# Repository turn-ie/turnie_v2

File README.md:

# turnie v2

ESP32-C3-MINI-1 と 64 個の WS2812B-2020（8x8）を 1 枚の基板に載せた turnie。

## ディレクトリ構成

| ディレクトリ | 内容 |
|---|---|
| `hardware/` | KiCad プロジェクト（`turnie_v2.kicad_pro`）、部品配置（`turnie_v2-all-pos.csv`） |
| `hardware/jlcpcb/` | JLCPCB に入稿したガーバーと PCBA 用ファイル |
| `hardware/*.pretty` | 自作フットプリント（EVQ-VVD00203B、サムホイール型可変抵抗） |

## ハードウェア

| 部品 | 内容 |
|---|---|
| MCU | ESP32-C3-MINI-1 |
| LED | WS2812B-2020 x 64（8x8） |
| 電源 | MIC5219-3.3（LDO）、USB-C |
| 入力 | タクトスイッチ x 3、サムホイール |

## 備考

- この版向けのファームウェアは収録していない。
- 画像は KiCad の 3D ビューから書き出したもの。

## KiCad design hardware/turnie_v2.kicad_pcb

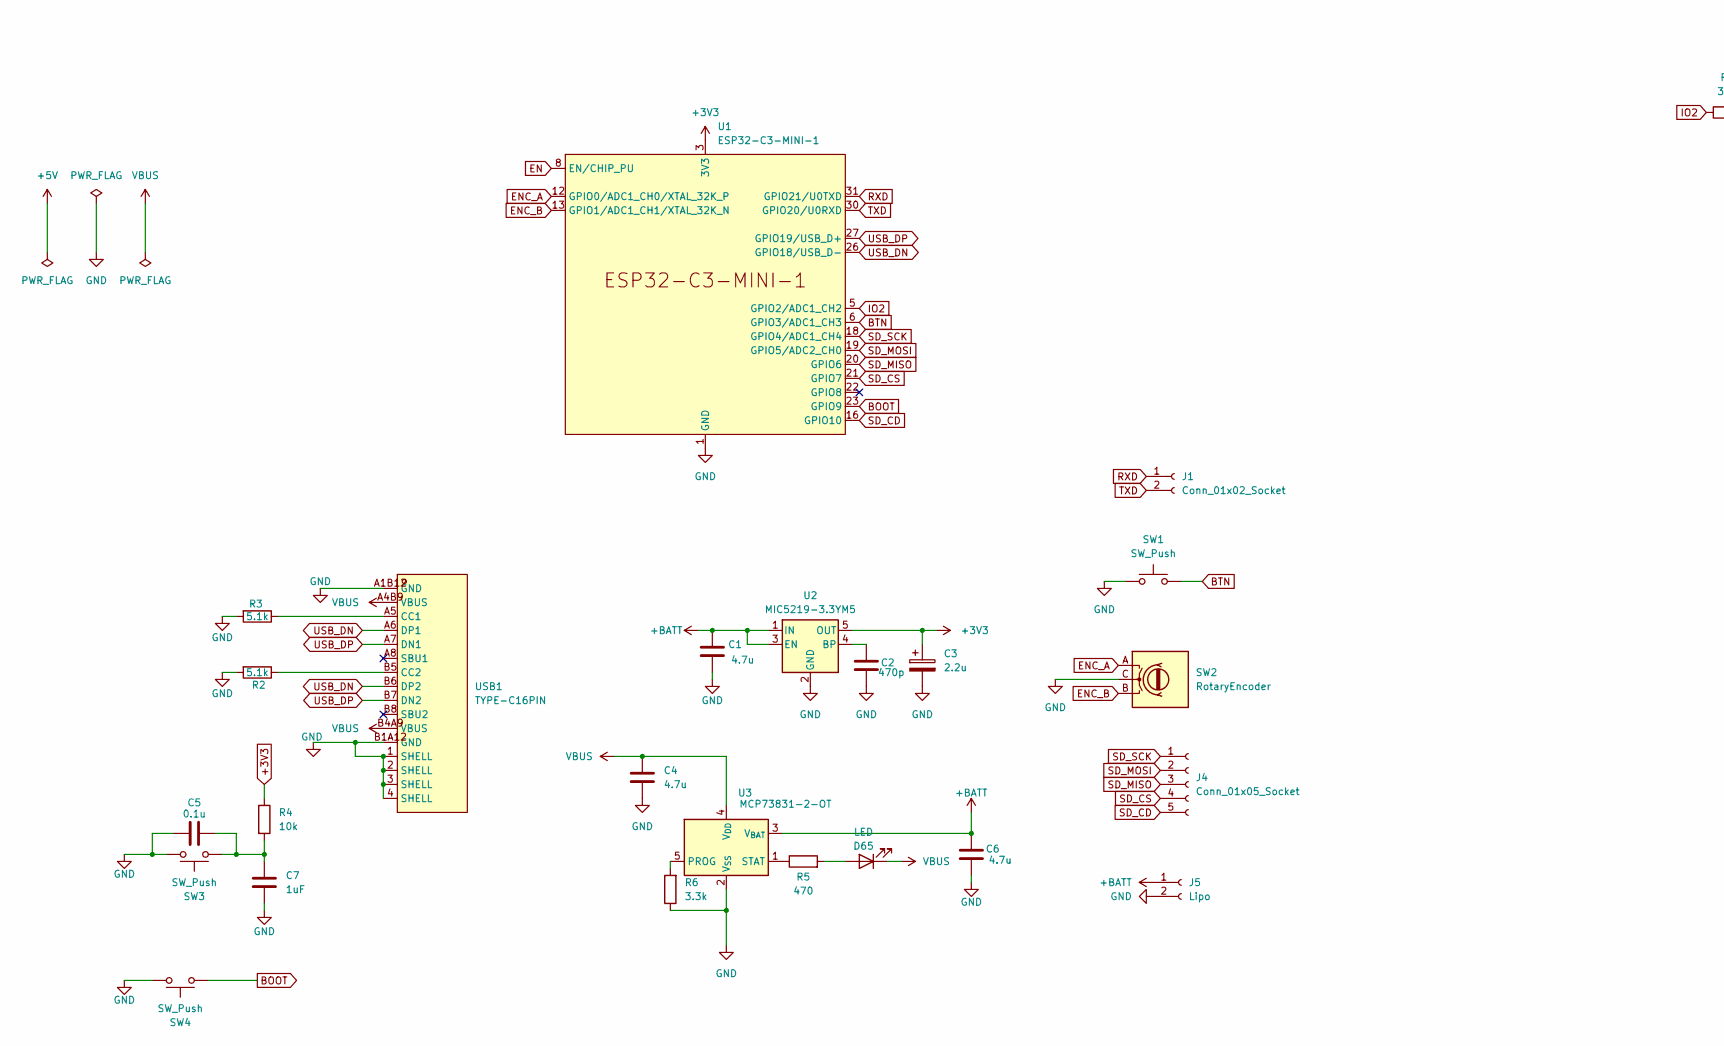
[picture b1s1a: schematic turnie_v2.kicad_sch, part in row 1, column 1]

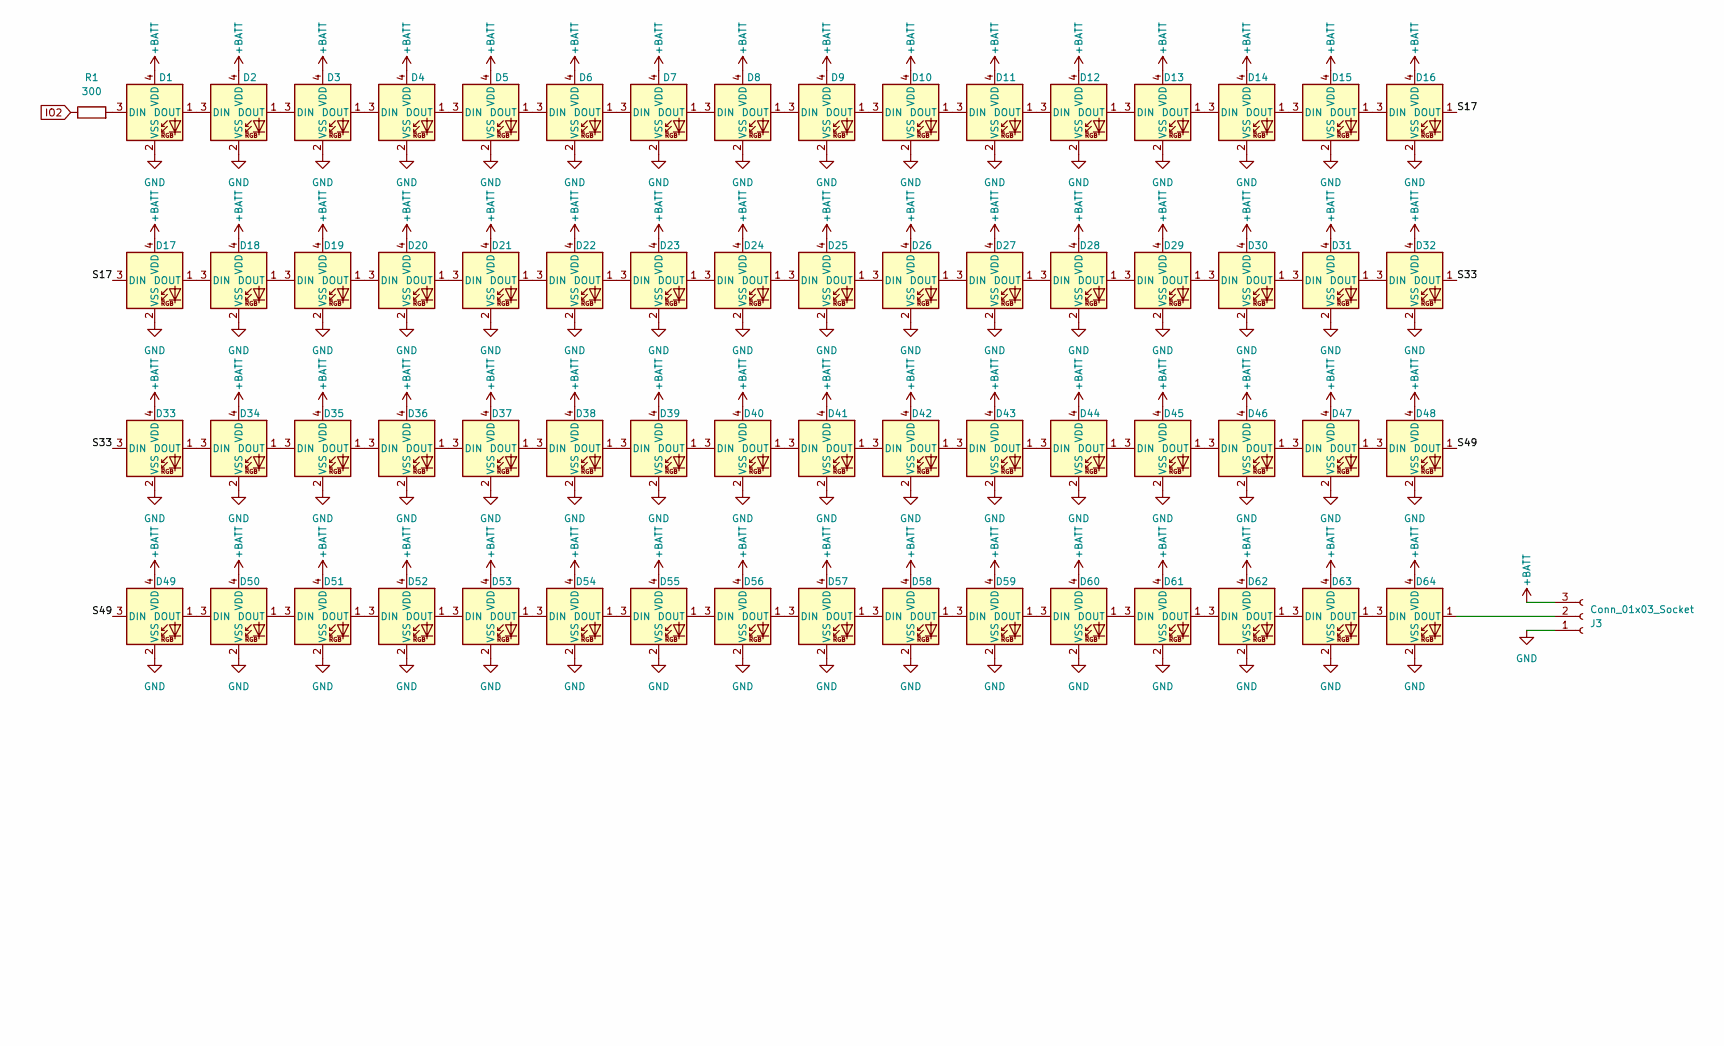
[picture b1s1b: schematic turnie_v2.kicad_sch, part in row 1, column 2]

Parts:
C1, C4, C6: 4.7u; C_0805_2012Metric
C2: 470p; C_0805_2012Metric
C3: 2.2u; C_0805_2012Metric
C5: 0.1u; C_0805_2012Metric
C7: 1uF; C_0402_1005Metric
D1, D2, D3, D4, D5, D6, D7, D8, D9, D10, D11, D12, D13, D14, D15, D16, D17, D18, D19, D20, D21, D22, D23, D24, D25, D26, D27, D28, D29, D30, D31, D32, D33, D34, D35, D36, D37, D38, D39, D40, D41, D42, D43, D44, D45, D46, D47, D48, D49, D50, D51, D52, D53, D54, D55, D56, D57, D58, D59, D60, D61, D62, D63, D64: WS2812B-2020; LED_WS2812B-2020_PLCC4_2.0x2.0mm
D65: LED; C_0805_2012Metric
J1: Conn_01x02_Socket; PinHeader_1x02_P2.54mm_Vertical
J3: Conn_01x03_Socket; PinSocket_1x03_P2.54mm_Vertical
J4: Conn_01x05_Socket; PinSocket_1x05_P2.54mm_Vertical
J5: Lipo; PinSocket_1x02_P2.54mm_Vertical
R1: 300; C_0402_1005Metric
R2, R3: 5.1k; C_0402_1005Metric
R4: 10k; C_0402_1005Metric
R5: 470; C_0402_1005Metric
R6: 3.3k; C_0402_1005Metric
SW1: SW_Push; SW_PUSH_6mm
SW2: RotaryEncoder; 名称未設定
SW3, SW4: SW_Push; SW_SPST_B3U-1000P
U1: ESP32-C3-MINI-1
U2: MIC5219-3.3YM5; SOT-23-5
U3: MCP73831-2-OT; SOT-23-5
USB1: TYPE-C16PIN; USB-C_SHOUHAN_TYPE-C16PIN_C393939; MPN TYPE-C16PIN; LCSC Part C393939

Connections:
+3V3: C3.1, R4.1, U1.3 (3V3), U2.5 (OUT)
+BATT: C1.1, C6.2, D1.4 (VDD), D2.4 (VDD), D3.4 (VDD), D4.4 (VDD), D5.4 (VDD), D6.4 (VDD), D7.4 (VDD), D8.4 (VDD), D9.4 (VDD), D10.4 (VDD), D11.4 (VDD), D12.4 (VDD), D13.4 (VDD), D14.4 (VDD), D15.4 (VDD), D16.4 (VDD), D17.4 (VDD), D18.4 (VDD), D19.4 (VDD), D20.4 (VDD), D21.4 (VDD), D22.4 (VDD), D23.4 (VDD), D24.4 (VDD), D25.4 (VDD), D26.4 (VDD), D27.4 (VDD), D28.4 (VDD), D29.4 (VDD), D30.4 (VDD), D31.4 (VDD), D32.4 (VDD), D33.4 (VDD), D34.4 (VDD), D35.4 (VDD), D36.4 (VDD), D37.4 (VDD), D38.4 (VDD), D39.4 (VDD), D40.4 (VDD), D41.4 (VDD), D42.4 (VDD), D43.4 (VDD), D44.4 (VDD), D45.4 (VDD), D46.4 (VDD), D47.4 (VDD), D48.4 (VDD), D49.4 (VDD), D50.4 (VDD), D51.4 (VDD), D52.4 (VDD), D53.4 (VDD), D54.4 (VDD), D55.4 (VDD), D56.4 (VDD), D57.4 (VDD), D58.4 (VDD), D59.4 (VDD), D60.4 (VDD), D61.4 (VDD), D62.4 (VDD), D63.4 (VDD), D64.4 (VDD), J3.3, J5.1, U2.1 (IN), U2.3 (EN), U3.3 (V_{BAT})
/S17: D16.1 (DOUT), D17.3 (DIN)
/S33: D32.1 (DOUT), D33.3 (DIN)
/S49: D48.1 (DOUT), D49.3 (DIN)
BOOT: SW4.2, U1.23 (GPIO9)
BTN: SW1.2, U1.6 (GPIO3/ADC1_CH3)
EN: U1.8 (EN/CHIP_PU)
ENC_A: SW2.A, U1.12 (GPIO0/ADC1_CH0/XTAL_32K_P)
ENC_B: SW2.B, U1.13 (GPIO1/ADC1_CH1/XTAL_32K_N)
GND: C1.2, C2.2, C3.2, C4.2, C5.1, C6.1, C7.2, D1.2 (VSS), D2.2 (VSS), D3.2 (VSS), D4.2 (VSS), D5.2 (VSS), D6.2 (VSS), D7.2 (VSS), D8.2 (VSS), D9.2 (VSS), D10.2 (VSS), D11.2 (VSS), D12.2 (VSS), D13.2 (VSS), D14.2 (VSS), D15.2 (VSS), D16.2 (VSS), D17.2 (VSS), D18.2 (VSS), D19.2 (VSS), D20.2 (VSS), D21.2 (VSS), D22.2 (VSS), D23.2 (VSS), D24.2 (VSS), D25.2 (VSS), D26.2 (VSS), D27.2 (VSS), D28.2 (VSS), D29.2 (VSS), D30.2 (VSS), D31.2 (VSS), D32.2 (VSS), D33.2 (VSS), D34.2 (VSS), D35.2 (VSS), D36.2 (VSS), D37.2 (VSS), D38.2 (VSS), D39.2 (VSS), D40.2 (VSS), D41.2 (VSS), D42.2 (VSS), D43.2 (VSS), D44.2 (VSS), D45.2 (VSS), D46.2 (VSS), D47.2 (VSS), D48.2 (VSS), D49.2 (VSS), D50.2 (VSS), D51.2 (VSS), D52.2 (VSS), D53.2 (VSS), D54.2 (VSS), D55.2 (VSS), D56.2 (VSS), D57.2 (VSS), D58.2 (VSS), D59.2 (VSS), D60.2 (VSS), D61.2 (VSS), D62.2 (VSS), D63.2 (VSS), D64.2 (VSS), J3.1, J5.2, R2.2, R3.2, R6.1, SW1.1, SW2.C, SW3.1, SW4.1, U1.1 (GND), U1.2 (GND), U1.11 (GND), U1.14 (GND), U1.36 (GND), U1.37 (GND), U1.38 (GND), U1.39 (GND), U1.40 (GND), U1.41 (GND), U1.42 (GND), U1.43 (GND), U1.44 (GND), U1.45 (GND), U1.46 (GND), U1.47 (GND), U1.48 (GND), U1.49 (GND), U1.50 (GND), U1.51 (GND), U1.52 (GND), U1.53 (GND), U2.2 (GND), U3.2 (V_{SS}), USB1.1 (SHELL), USB1.2 (SHELL), USB1.3 (SHELL), USB1.4 (SHELL), USB1.A1B12 (GND), USB1.B1A12 (GND)
IO2: R1.1, U1.5 (GPIO2/ADC1_CH2)
unnamed: C5.2, C7.1, R4.2, SW3.2
unnamed: D1.3 (DIN), R1.2
unnamed: D1.1 (DOUT), D2.3 (DIN)
unnamed: D2.1 (DOUT), D3.3 (DIN)
unnamed: D3.1 (DOUT), D4.3 (DIN)
unnamed: D4.1 (DOUT), D5.3 (DIN)
unnamed: D5.1 (DOUT), D6.3 (DIN)
unnamed: D6.1 (DOUT), D7.3 (DIN)
unnamed: D7.1 (DOUT), D8.3 (DIN)
unnamed: D8.1 (DOUT), D9.3 (DIN)
unnamed: D9.1 (DOUT), D10.3 (DIN)
unnamed: D10.1 (DOUT), D11.3 (DIN)
unnamed: D11.1 (DOUT), D12.3 (DIN)
unnamed: D12.1 (DOUT), D13.3 (DIN)
unnamed: D13.1 (DOUT), D14.3 (DIN)
unnamed: D14.1 (DOUT), D15.3 (DIN)
unnamed: D15.1 (DOUT), D16.3 (DIN)
unnamed: D17.1 (DOUT), D18.3 (DIN)
unnamed: D18.1 (DOUT), D19.3 (DIN)
unnamed: D19.1 (DOUT), D20.3 (DIN)
unnamed: D20.1 (DOUT), D21.3 (DIN)
unnamed: D21.1 (DOUT), D22.3 (DIN)
unnamed: D22.1 (DOUT), D23.3 (DIN)
unnamed: D23.1 (DOUT), D24.3 (DIN)
unnamed: D24.1 (DOUT), D25.3 (DIN)
unnamed: D25.1 (DOUT), D26.3 (DIN)
unnamed: D26.1 (DOUT), D27.3 (DIN)
unnamed: D27.1 (DOUT), D28.3 (DIN)
unnamed: D28.1 (DOUT), D29.3 (DIN)
unnamed: D29.1 (DOUT), D30.3 (DIN)
unnamed: D30.1 (DOUT), D31.3 (DIN)
unnamed: D31.1 (DOUT), D32.3 (DIN)
unnamed: D33.1 (DOUT), D34.3 (DIN)
unnamed: D34.1 (DOUT), D35.3 (DIN)
unnamed: D35.1 (DOUT), D36.3 (DIN)
unnamed: D36.1 (DOUT), D37.3 (DIN)
unnamed: D37.1 (DOUT), D38.3 (DIN)
unnamed: D38.1 (DOUT), D39.3 (DIN)
unnamed: D39.1 (DOUT), D40.3 (DIN)
unnamed: D40.1 (DOUT), D41.3 (DIN)
unnamed: D41.1 (DOUT), D42.3 (DIN)
unnamed: D42.1 (DOUT), D43.3 (DIN)
unnamed: D43.1 (DOUT), D44.3 (DIN)
unnamed: D44.1 (DOUT), D45.3 (DIN)
unnamed: D45.1 (DOUT), D46.3 (DIN)
unnamed: D46.1 (DOUT), D47.3 (DIN)
unnamed: D47.1 (DOUT), D48.3 (DIN)
unnamed: D49.1 (DOUT), D50.3 (DIN)
unnamed: D50.1 (DOUT), D51.3 (DIN)
unnamed: D51.1 (DOUT), D52.3 (DIN)
unnamed: D52.1 (DOUT), D53.3 (DIN)
unnamed: D53.1 (DOUT), D54.3 (DIN)
unnamed: D54.1 (DOUT), D55.3 (DIN)
unnamed: D55.1 (DOUT), D56.3 (DIN)
unnamed: D56.1 (DOUT), D57.3 (DIN)
unnamed: D57.1 (DOUT), D58.3 (DIN)
unnamed: D58.1 (DOUT), D59.3 (DIN)
unnamed: D59.1 (DOUT), D60.3 (DIN)
unnamed: D60.1 (DOUT), D61.3 (DIN)
unnamed: D61.1 (DOUT), D62.3 (DIN)
unnamed: D62.1 (DOUT), D63.3 (DIN)
unnamed: D63.1 (DOUT), D64.3 (DIN)
unnamed: D64.1 (DOUT), J3.2
unnamed: D65.2 (A), R5.2
unnamed: C2.1, U2.4 (BP)
unnamed: R6.2, U3.5 (PROG)
unnamed: R5.1, U3.1 (STAT)
unnamed: R3.1, USB1.A5 (CC1)
unnamed: R2.1, USB1.B5 (CC2)
RXD: J1.1, U1.31 (GPIO21/U0TXD)
SD_CD: J4.5, U1.16 (GPIO10)
SD_CS: J4.4, U1.21 (GPIO7)
SD_MISO: J4.3, U1.20 (GPIO6)
SD_MOSI: J4.2, U1.19 (GPIO5/ADC2_CH0)
SD_SCK: J4.1, U1.18 (GPIO4/ADC1_CH4)
TXD: J1.2, U1.30 (GPIO20/U0RXD)
USB_DN: U1.26 (GPIO18/USB_D-), USB1.A6 (DP1), USB1.B6 (DP2)
USB_DP: U1.27 (GPIO19/USB_D+), USB1.A7 (DN1), USB1.B7 (DN2)
VBUS: C4.1, D65.1 (K), U3.4 (V_{DD}), USB1.A4B9 (VBUS), USB1.B4A9 (VBUS)

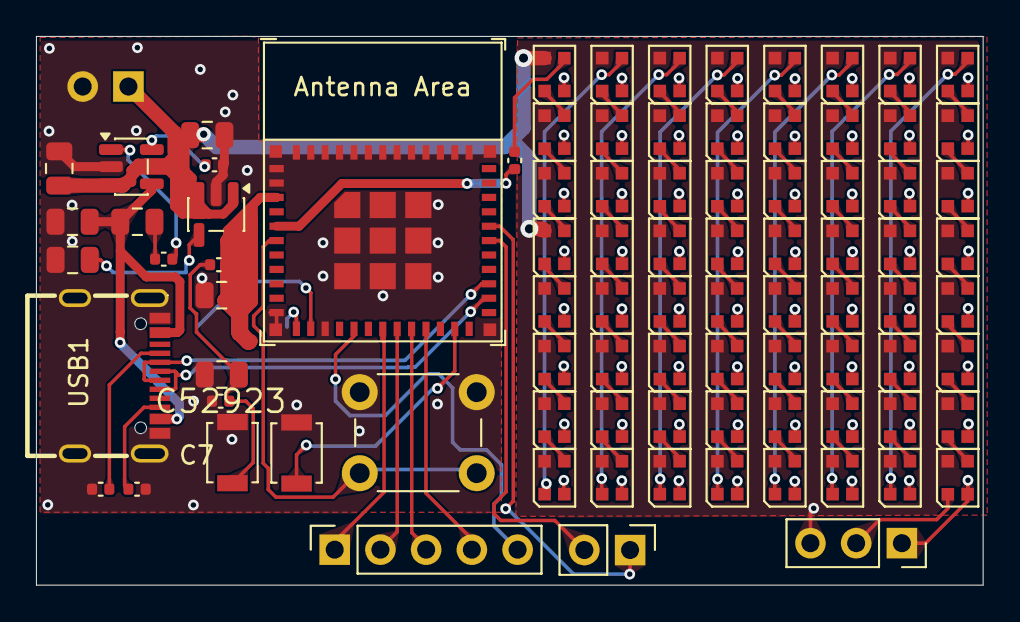
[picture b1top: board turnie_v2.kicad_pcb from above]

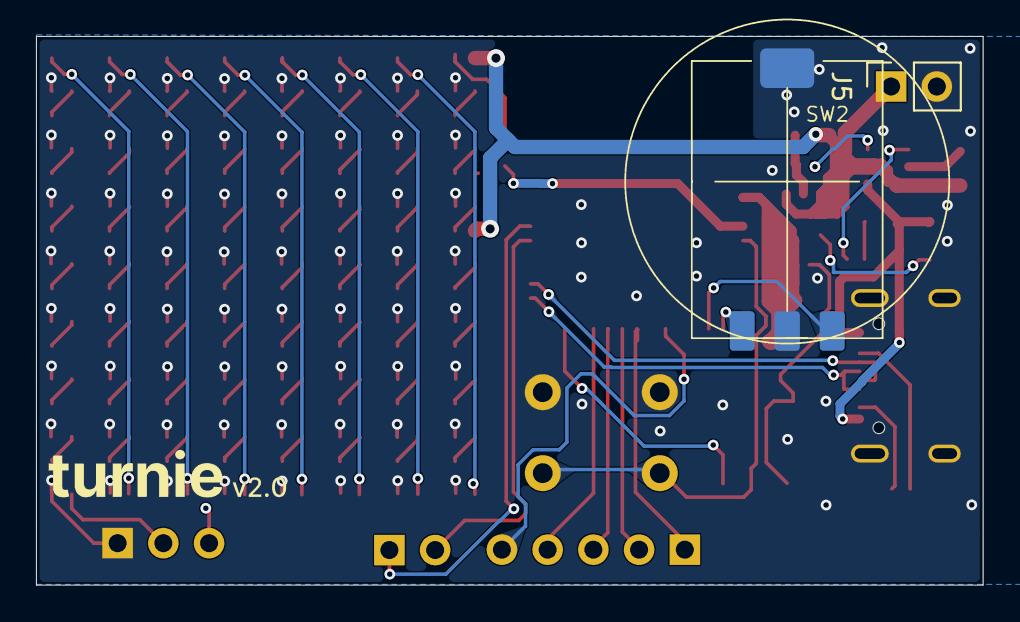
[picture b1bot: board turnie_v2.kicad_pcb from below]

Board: 2 copper layers, 52.6 x 30.5 mm, 90 parts (2 on the bottom side), 90 nets.

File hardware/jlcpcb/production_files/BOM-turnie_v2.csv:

Comment,Designator,Footprint,LCSC,Quantity
0.1u,C5,C_0805_2012Metric,C126469,1
10k,R4,C_0402_1005Metric,C25744,1
1uF,C7,C_0402_1005Metric,C52923,1
2.2u,C3,C_0805_2012Metric,C377773,1
3.3k,R6,C_0402_1005Metric,C25890,1
300,R1,C_0402_1005Metric,C25159,1
4.7u,"C1,C4,C6",C_0805_2012Metric,C1746,3
470,R5,C_0402_1005Metric,C25117,1
470p,C2,C_0805_2012Metric,C1743,1
5.1k,"R2,R3",C_0402_1005Metric,C25905,2
ESP32-C3-MINI-1,U1,ESP32-C3-MINI-1,C2838502,1
LED,D65,C_0805_2012Metric,C2297,1
MCP73831-2-OT,U3,SOT-23-5,C14879,1
MIC5219-3.3YM5,U2,SOT-23-5,C29613,1
TYPE-C16PIN,USB1,USB-C_SHOUHAN_TYPE-C16PIN_C393939,C393939,1
WS2812B-2020,"D1,D10,D11,D12,D13,D14,D15,D16,D17,D18,D19,D2,D20,D21,D22,D23,D24,D25,D26,D27,D28,D29,D3,D30,D31,D32,D33,D34,D35,D36,D37,D38,D39,D4,D40,D41,D42,D43,D44,D45,D46,D47,D48,D49,D5,D50,D51,D52,D53,D54,D55,D56,D57,D58,D59,D6,D60,D61,D62,D63,D64,D7,D8,D9",LED_WS2812B-2020_PLCC4_2.0x2.0mm,C965555,64
Conn_01x03_Socket,J3,PinSocket_1x03_P2.54mm_Vertical,,1
SW_Push,SW3,SW_SPST_B3U-1000P,,1
Conn_01x02_Socket,J1,PinHeader_1x02_P2.54mm_Vertical,,1
Conn_01x05_Socket,J4,PinSocket_1x05_P2.54mm_Vertical,,1
SW_Push,SW1,SW_PUSH_6mm,,1
SW_Push,SW4,SW_SPST_B3U-1000P,,1
Lipo,J5,PinSocket_1x02_P2.54mm_Vertical,,1
RotaryEncoder,SW2,名称未設定,,1
